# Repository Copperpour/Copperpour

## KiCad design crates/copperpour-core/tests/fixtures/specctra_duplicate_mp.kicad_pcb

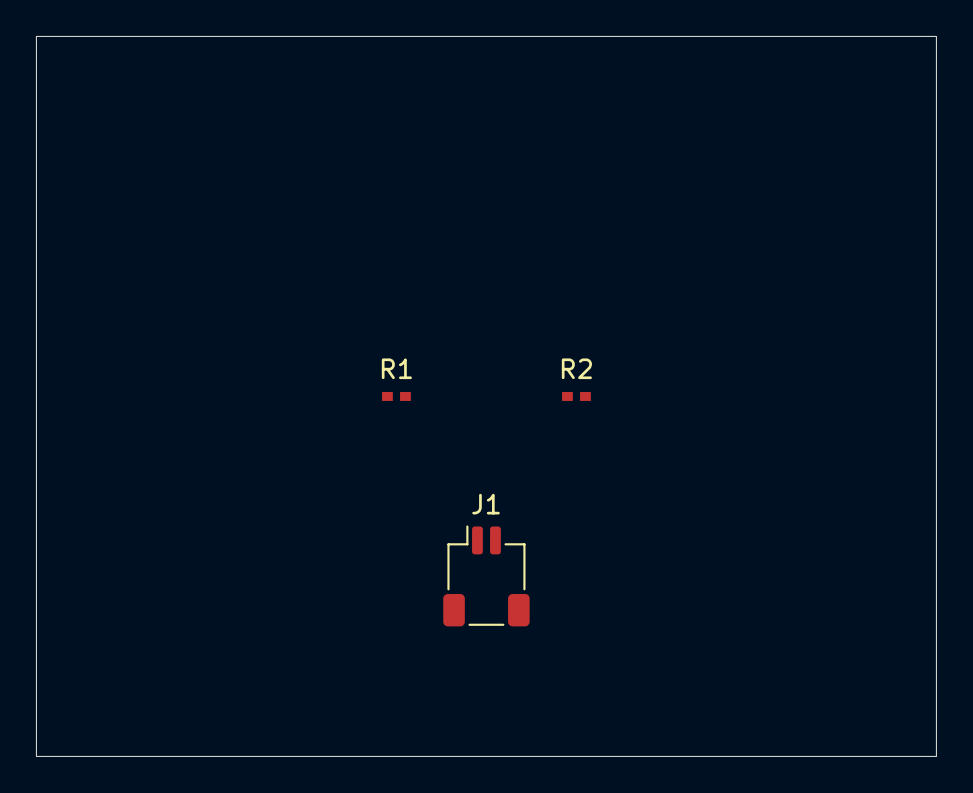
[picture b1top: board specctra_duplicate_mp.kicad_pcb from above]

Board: 2 copper layers, 50.0 x 40.0 mm, 3 parts (0 on the bottom side), 2 nets, no tracks yet.

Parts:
J1: SH 2P; JST_SH_SM02B-SRSS-TB_1x02-1MP_P1.00mm_Horizontal
R1: 10k; R_0402
R2: 4.7k; R_0402

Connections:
GND: J1.2, J1.MP, R1.2, R2.1
VCC: J1.1, R1.1, R2.2

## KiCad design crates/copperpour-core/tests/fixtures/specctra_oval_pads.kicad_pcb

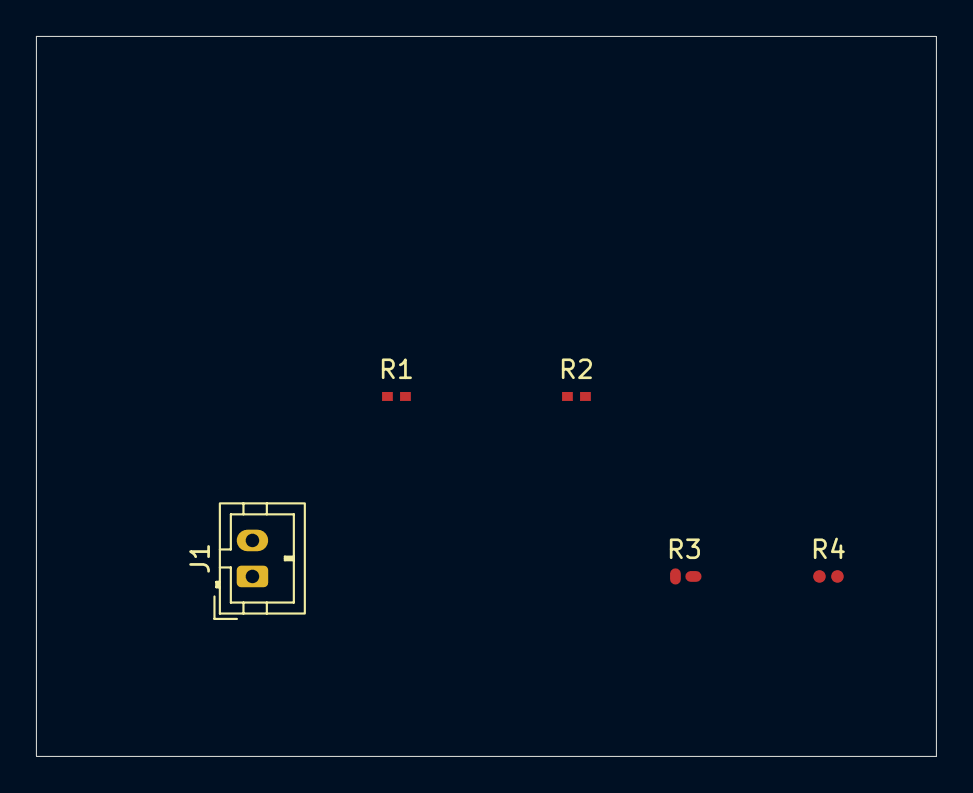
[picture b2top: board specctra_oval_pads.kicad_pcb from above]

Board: 2 copper layers, 50.0 x 40.0 mm, 5 parts (0 on the bottom side), 2 nets, no tracks yet.

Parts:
J1: PH 2P; JST_PH_B2B-PH-K_1x02_P2.00mm_Vertical
R1: 10k; R_0402
R2, R3, R4: 4.7k; R_0402

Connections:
GND: J1.2, R1.2, R2.1, R3.2, R4.2
VCC: J1.1, R1.1, R2.2, R3.1, R4.1

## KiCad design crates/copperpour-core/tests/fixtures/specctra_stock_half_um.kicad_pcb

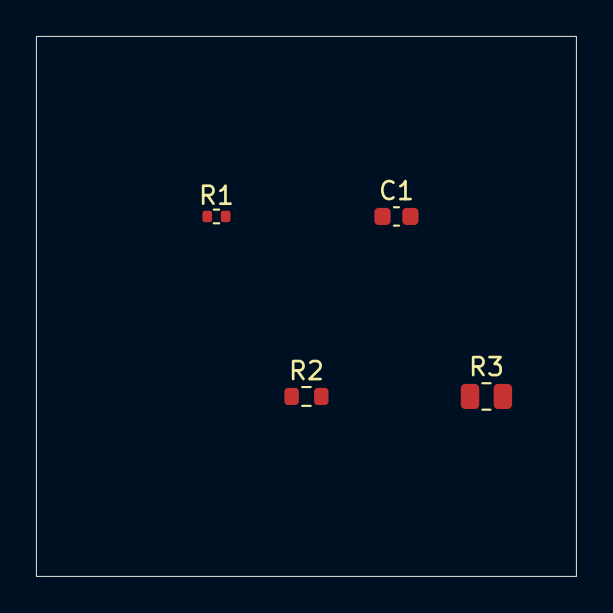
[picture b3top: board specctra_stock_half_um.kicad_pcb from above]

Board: 2 copper layers, 30.0 x 30.0 mm, 4 parts (0 on the bottom side), 3 nets, no tracks yet.

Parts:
C1: C_0603_1608Metric
R1: R_0402_1005Metric
R2: R_0603_1608Metric
R3: R_0805_2012Metric

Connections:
GND: C1.2, R2.2, R3.2
SIG: C1.1, R1.2
VCC: R1.1, R2.1, R3.1
